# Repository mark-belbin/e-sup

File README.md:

# eSUP
HW and FW for motorized stand up paddle board (SUP). Includes BMS+Charger, MCU, and Battery-Holder PCBA designs.

## Motivation
1. Cruise around Foster City on a battery powered electric SUP.
2. Learn more about BMS HW and design.
3. Improve STM32 FW skills and knowledge.

## High-Level Block Diagram
Some aspects still TBD, but this is the general idea so far. BMS+Charger PCBA, Battery-Holder PCBAs, and MCU PCBA. May or may not need another custom PCBA for hand controller, might be possible to directly use or modify an OTS hand controller normally used for electric foil boards or skateboards.

## Battery Configuration

## Power Architecture

## Mechanical Design

## PCBA Design

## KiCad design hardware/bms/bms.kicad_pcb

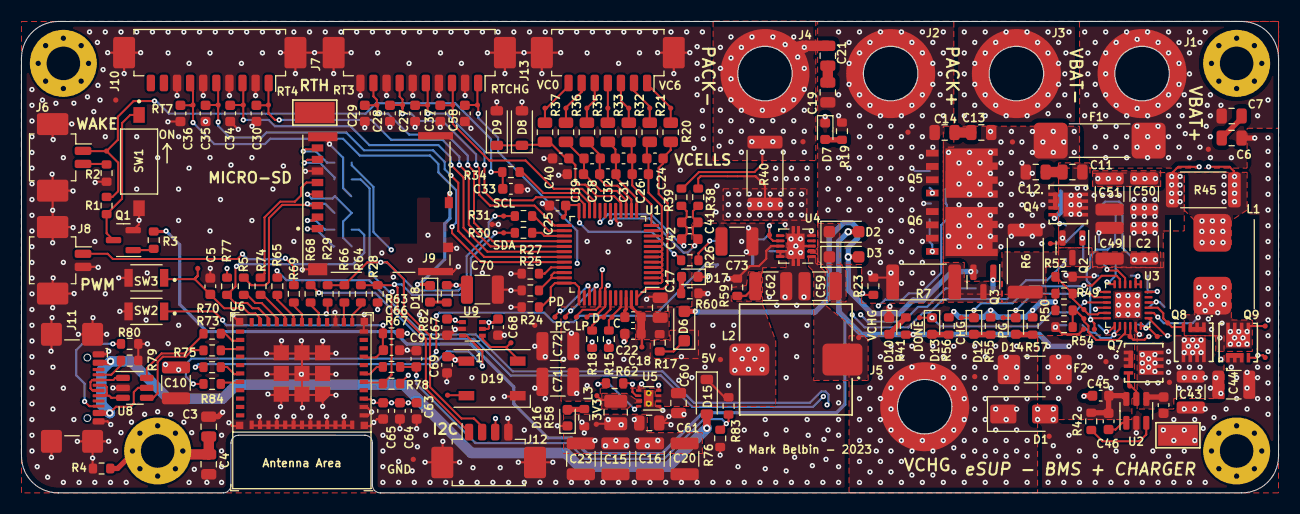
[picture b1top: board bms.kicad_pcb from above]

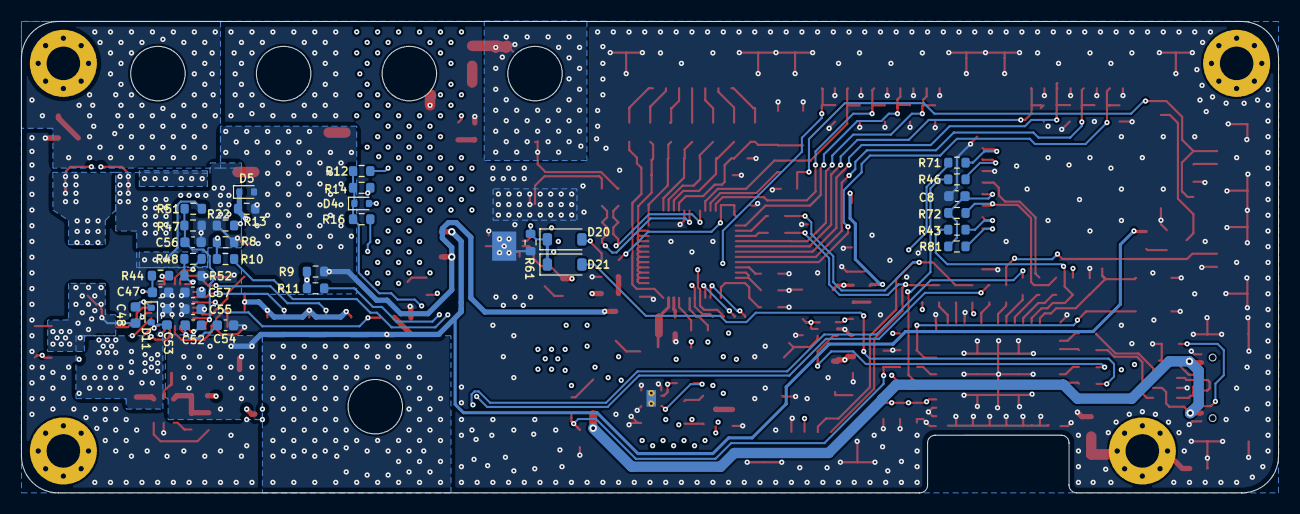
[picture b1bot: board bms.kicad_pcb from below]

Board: 4 copper layers, 120.0 x 45.0 mm, 287 parts (34 on the bottom side), 144 nets.

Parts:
C1, C5, C8, C9, C33, C42, C45, C46, C48, C52, C54, C65, C67, C68, C69: 0.1uF; C_0603_1608Metric
C2, C43, C44, C49, C50, C51: 10uF; C_1210_3225Metric
C3, C4, C6, C7, C11, C12, C13, C14, C19, C21: 0.1uF; C_0805_2012Metric
C10, C15, C16, C20, C23, C70, C71, C72, C73: 100uF; C_1210_3225Metric
C17: 1uF; C_0805_2012Metric
C18, C41: 100pF; C_0603_1608Metric
C22: 470nF; C_0603_1608Metric
C24, C26, C31, C32, C38, C39, C40: 220nF; C_0603_1608Metric
C25: 2.2uF; C_0603_1608Metric
C27, C28, C29, C30, C34, C35, C36, C37, C58: 1nF; C_0603_1608Metric
C47, C53, C55, C66: 1uF; C_0603_1608Metric
C56: 22pF; C_0603_1608Metric
C57: 56nF; C_0603_1608Metric
C59: 2.2uF; C_1210_3225Metric
C60: 10uF; C_0805_2012Metric
C61: 22uF; C_0805_2012Metric
C62: 47uF; C_1210_3225Metric
C63, C64: 10uF; C_0603_1608Metric
D1: SMAJ28A; D_SMA
D2, D3, D6: D_Schottky; D_SOD-123F
D4, D5: D_Zener; D_SOD-523
D7, D10, D13: BLUE; LED_0603_1608Metric
D8, D15, D20, D21: D_Schottky; D_SOD-123
D9: D_Zener; D_SOD-123
D11: D_Schottky; D_SOD-523
D12: AMBER; LED_0603_1608Metric
D14, D16, D17, D18: GREEN; LED_0603_1608Metric
D19: WS2812B; LED_WS2812B_PLCC4_5.0x5.0mm_P3.2mm
F1: 60A; SF-3812F6000T-2
F2: 15A; FUSC6125X279N
H1, H2, H3, H4: MountingHole_Pad; MountingHole_3.2mm_M3_Pad_Via
J1, J2, J3, J4, J5: Screw_Terminal_01x01; Wurth_746600430R
J6, J8: Conn_01x02; Molex_PicoBlade_53261-0271_1x02-1MP_P1.25mm_Horizontal
J7, J10: Conn_01x10; Molex_PicoBlade_53261-1071_1x10-1MP_P1.25mm_Horizontal
J9: Micro_SD_Card_Det2; MOLEX_503398-1892
J11: USB_C_Receptacle_USB2.0; USB_C_Receptacle_GCT_USB4110
J12: Conn_01x03; Molex_PicoBlade_53261-0471_1x04-1MP_P1.25mm_Horizontal
J13: Conn_01x07; Molex_PicoBlade_53261-0771_1x07-1MP_P1.25mm_Horizontal
L1: 3.3uH; IND_ETQP5M3R3YFK
L2: 150uH; IND_1050P-WE-PD_WRE-L
L3: 3.3uH; L_1008_2520Metric
NT1, NT2, NT4, NT5: Net-Tie; NetTie-2_SMD_Pad_8mil
Q1: MMBT3904; SOT-23
Q2, Q3: Q_PMOS_GSD; SOT-23
Q4, Q7, Q8, Q9: BSZ018N04LS6ATMA1; PG-TSDSON-8-26_INF
Q5, Q6: IAUC120N04S6N006ATMA1; PG-TDSON-8
R1, R2, R18, R19, R22, R23, R41, R42, R63, R71, R72, R76, R77, R78, R81, R83: 10k; R_0603_1608Metric
R3, R26, R55, R57, R58, R60, R82, R84: 1k; R_0603_1608Metric
R4, R8, R9, R12, R13: 10M; R_0603_1608Metric
R5, R24, R27, R30, R31, R34, R43, R46, R64, R65, R66, R67, R68, R69, R70, R73, R74, R75: 0R; R_0603_1608Metric
R6, R7: 1k; R_2512_6332Metric
R10, R11, R15, R79, R80: 5.1k; R_0603_1608Metric
R14, R16: 51; R_0603_1608Metric
R17, R38, R39, R56: 100R; R_0603_1608Metric
R20, R21, R32, R33, R35, R36, R37: 30R; R_0805_2012Metric
R25, R49, R50, R62: 100k; R_0603_1608Metric
R28, R29: 2.2k; R_0603_1608Metric
R40: 1m; R_2512_6332Metric
R44: 10R; R_0603_1608Metric
R45: 10m; R_2512_6332Metric
R47: 330k; R_0603_1608Metric
R48: 9.31k; R_0603_1608Metric
R51: 30k; R_0603_1608Metric
R52: 430k; R_0603_1608Metric
R53: 137k; R_0603_1608Metric
R54: 44.2k; R_0603_1608Metric
R59: 0.11R; R_0603_1608Metric
R61: 1.5M; R_0603_1608Metric
SW1: SW_SPST; SW_DS04-254-2-01BK-SMT-TR
SW2, SW3: SW_Push; SW_B3U-1000P
TP1, TP2, TP3, TP4, TP5, TP6, TP7, TP8, TP9, TP10, TP11, TP12, TP13, TP14, TP15, TP16, TP19, TP20, TP21, TP22, TP23, TP24, TP25, TP26, TP27, TP28, TP29, TP30, TP31, TP32, TP33, TP34, TP35, TP36, TP37, TP38, TP39, TP40, TP42, TP43, TP44, TP45, TP46, TP47, TP48, TP49, TP50, TP51, TP52, TP53, TP54, TP55, TP56, TP57, TP58, TP59, TP60, TP61, TP62, TP63, TP64: TestPoint; TestPoint_Pad_D0.5mm
TP17, TP18: TestPoint; TestPoint_Keystone_5019_Minature
U1: BQ76952; TQFP-48_7x7mm_P0.5mm
U2: LM74700; SOT-23-6
U3: BQ24610; VQFN-24-1EP_4x4mm_P0.5mm_EP2.45x2.45mm
U4: LM5166X; Texas_S-PVSON-N10_ThermalVias
U5: TPS62172DSG; WSON-8-1EP_2x2mm_P0.5mm_EP0.9x1.6mm_ThermalVias
U6: ESP32-C3-MINI-1-N4; ESP32-C3-MINI-1
U8: USBLC6-2SC6; SOT-23-6
U9: TXU0101DCKR; SOT-363_SC-70-6

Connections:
+3V3: C8.1, C10.1, C15.1, C16.1, C20.1, C23.1, C61.1, C63.1, C64.1, C65.1, C67.1, C70.1, J9.4 (VDD), J12.3, L3.2, R28.1, R29.1, R58.2, R62.2, R63.1, R71.1, R72.1, R77.1, R78.1, R81.1, R82.2, TP60.1, U5.6 (VOS), U6.3 (3V3), U9.1 (VCCA)
+5V: C60.1, C68.1, C69.1, C71.1, C72.1, C73.1, D15.1 (K), D19.1 (VDD), L2.2, R59.2, R60.2, R83.1, TP58.1, U4.8 (VOUT), U5.2 (VIN), U5.3 (EN), U9.5 (OE), U9.6 (VCCB)
/BATTERY BALANCE AND MONITOR/CGATE: D5.1 (K), Q4.2 (G), R13.2, R15.1
/BATTERY BALANCE AND MONITOR/CHG: R15.2, TP7.1, U1.45 (CHG)
/BATTERY BALANCE AND MONITOR/DGATE: D4.1 (K), R12.2, R14.2, R16.2, R18.1
/BATTERY BALANCE AND MONITOR/DSG: R18.2, TP8.1, U1.43 (DSG)
/BATTERY BALANCE AND MONITOR/I2C_SCL: J12.2, R29.2, R31.2, R66.1, TP22.1
/BATTERY BALANCE AND MONITOR/I2C_SDA: J12.1, R28.2, R30.2, R64.1, TP21.1
/BATTERY BALANCE AND MONITOR/LD: R23.1, TP15.1, U1.41 (LD)
/BATTERY BALANCE AND MONITOR/PACK: R22.1, TP14.1, U1.42 (PACK)
/BATTERY BALANCE AND MONITOR/PACK+: C14.2, C19.2, D4.2 (A), J2.1, Q5.1 (S), Q6.1 (S), R7.2, R12.1, R19.1, R23.2, TP4.1
/BATTERY BALANCE AND MONITOR/PACK-: C21.1, J4.1, NT2.2, R40.1, TP9.1
/BATTERY BALANCE AND MONITOR/PCGATE: Q2.1 (G), R8.2, R10.1
/BATTERY BALANCE AND MONITOR/PCHG: R10.2, TP10.1, U1.40 (PCHG)
/BATTERY BALANCE AND MONITOR/PDGATE: Q3.1 (G), R9.2, R11.1
/BATTERY BALANCE AND MONITOR/PDSG: R11.2, TP12.1, U1.39 (PDSG)
/BATTERY BALANCE AND MONITOR/PWR_EN: D20.2 (A), R26.1
/BATTERY BALANCE AND MONITOR/REG18: C25.1, R26.2, TP16.1, U1.24 (REG18)
/BATTERY BALANCE AND MONITOR/RST_SHUT: R27.1, U1.33 (RST_SHUT)
/BATTERY BALANCE AND MONITOR/SCL_BMGT: R31.1, U1.26 (SCL)
/BATTERY BALANCE AND MONITOR/SDA_BMGT: R30.1, U1.27 (SDA)
/BATTERY BALANCE AND MONITOR/SRN: C41.1, C42.1, R39.1, U1.20 (SRN)
/BATTERY BALANCE AND MONITOR/SRP: C41.2, C42.2, R38.1, U1.18 (SRP)
/BATTERY BALANCE AND MONITOR/TS2: R34.1, U1.22 (WAKE/TS2)
/BATTERY BALANCE AND MONITOR/VC0: C40.1, D8.1 (K), D9.1 (K), R37.1, U1.16 (VC0)
/BATTERY BALANCE AND MONITOR/VC1: C38.2, C39.1, R36.1, U1.15 (VC1)
/BATTERY BALANCE AND MONITOR/VC2: C32.2, C38.1, R35.1, U1.14 (VC2)
/BATTERY BALANCE AND MONITOR/VC3: C31.2, C32.1, R33.1, U1.13 (VC3)
/BATTERY BALANCE AND MONITOR/VC4: C26.2, C31.1, R32.1, U1.12 (VC4)
/BATTERY BALANCE AND MONITOR/VC15: C24.2, C26.1, R21.1, U1.1 (VC15), U1.2 (VC14), U1.3 (VC13), U1.4 (VC12), U1.5 (VC11), U1.6 (VC10), U1.7 (VC9), U1.8 (VC8), U1.9 (VC7), U1.10 (VC6), U1.11 (VC5)
/BATTERY BALANCE AND MONITOR/VC16: C24.1, R20.1, U1.48 (VC16)
/BATTERY BALANCE AND MONITOR/VCHG+: C2.1, C11.1, C49.1, C50.1, C51.1, C56.1, NT5.1, Q2.2 (S), Q4.3 (D), R8.1, R22.2, R45.1, R47.2, TP3.1
/BATTERY CHARGER/BTST: C48.2, D11.1 (K), U3.22 (BTST)
/BATTERY CHARGER/CHG_IN_PROT: C1.2, C43.1, C44.1, Q7.3 (D), Q8.3 (D), R44.1, TP38.1, U2.4 (CATHODE), U3.1 (ACN), U3.2 (ACP)
/BATTERY CHARGER/C_VCC: C47.1, R44.2, U3.24 (VCC)
/BATTERY CHARGER/DG: Q7.2 (G), TP39.1, U2.5 (GATE)
/BATTERY CHARGER/DRV_HI: Q8.2 (G), TP40.1, U3.21 (HIDRV)
/BATTERY CHARGER/DRV_LO: Q9.2 (G), TP44.1, U3.19 (LODRV)
/BATTERY CHARGER/ISET1: R49.1, R53.2, TP48.1, U3.11 (ISET1)
/BATTERY CHARGER/ISET2: R50.1, R54.2, TP49.1, U3.15 (ISET2)
/BATTERY CHARGER/REGEN: C53.1, D11.2 (A), TP43.1, U3.18 (REGEN)
/BATTERY CHARGER/SRN_CHG: C52.1, NT5.2, U3.13 (SRN)
/BATTERY CHARGER/SRP_CHG: C52.2, C54.1, NT4.2, U3.14 (SRP)
/BATTERY CHARGER/SW_NODE: C48.1, L1.1, Q8.1 (S), Q9.3 (D), TP42.1, U3.20 (PH)
/BATTERY CHARGER/TTC: C57.1, U3.7 (TTC)
/BATTERY CHARGER/VFB: C56.2, R47.1, R51.2, TP46.1, U3.12 (VFB)
/BATTERY CHARGER/VREF: C55.1, R48.2, R49.2, R50.2, R55.2, R56.2, R57.2, TP45.1, U3.4 (CE), U3.10 (VREF), U3.16 (ACSET)
/BATTERY CHARGER/~PG: D14.1 (K), TP56.1, U3.8 (~PG)
/BMS_WAKE: C33.2, J6.1, R1.1, R34.2, TP29.1
/CHG_STAT1: D12.1 (K), R65.1, TP54.1, U3.5 (STAT1)
/CHG_STAT2: D13.1 (K), R68.2, TP55.1, U3.9 (STAT2)
/MCU/3V3_SW: L3.1, TP59.1, U5.7 (SW)
/MCU/5V_DETECT: C9.1, R67.1, R76.1, R83.2
/MCU/5V_EN: D20.1 (K), D21.1 (K), R61.2, TP61.1, U4.7 (EN)
/MCU/5V_SW: L2.1, TP57.1, U4.1 (SW)
/MCU/BOOT: C5.1, SW3.1, TP62.1, U6.23 (IO9)
/MCU/CS: J9.2 (DAT3/CD), R43.2
/MCU/EN: C66.1, R63.2, SW2.1, U6.8 (EN)
/MCU/GPIO0: R64.2, U6.12 (IO0)
/MCU/GPIO1: R66.2, U6.13 (IO1)
/MCU/GPIO2: R46.2, R78.2, U6.5 (IO2)
/MCU/GPIO3: R67.2, U6.6 (IO3)
/MCU/GPIO4: R69.2, U6.18 (IO4)
/MCU/GPIO5: R65.2, U6.19 (IO5)
/MCU/GPIO6: R74.2, U6.20 (IO6)
/MCU/GPIO7: R5.1, U6.21 (IO7)
/MCU/GPIO8: R43.1, R77.2, U6.22 (IO8)
/MCU/GPIO10: R68.1, U6.16 (IO10)
/MCU/GPIO18: R70.1, U6.26 (IO18/USB_D-)
/MCU/GPIO19: R73.1, U6.27 (IO19/USB_D+)
/MCU/GPIO20: R75.2, U6.30 (RXD0)
/MCU/GPIO21: R84.1, U6.31 (TXD0)
/MCU/MCU_VIN: C59.1, D2.1 (K), D3.1 (K), U4.2 (VIN)
/MCU/MISO: J9.7 (DAT0), R46.1
/MCU/MOSI: J9.3 (CMD), R5.2, R72.2
/MCU/PG: R62.1, U5.8 (PG)
/MCU/PWM_OUT: J8.1, R69.1
/MCU/RGB_DIN: D19.4 (DIN), TP63.1, U9.4 (Y)
/MCU/RGB_DIN_ESP: R75.1, U9.3 (A)
/MCU/RGB_DOUT: D19.2 (DOUT), TP64.1
/MCU/SCLK: J9.5 (CLK), R74.1
/MCU/SD_CARD_WRITE: D21.2 (A), R84.2
/THERM_0: C37.1, J7.3, TP33.1, U1.21 (TS1)
/THERM_1: C27.1, J7.5, TP23.1, U1.23 (TS3)
/THERM_2: C28.1, J7.7, TP24.1, U1.25 (ALERT/TS4)
/THERM_3: C29.1, J7.9, TP25.1, U1.28 (HDQ/TS5)
/THERM_4: C30.1, J10.1, TP26.1, U1.29 (CFETOFF/TS6)
/THERM_5: C34.1, J10.3, TP30.1, U1.30 (DFETOFF/TS7)
/THERM_6: C35.1, J10.5, TP31.1, U1.31 (DCHG/TS8)
/THERM_7: C36.1, J10.7, TP32.1, U1.32 (DDSG/TS9)
/THERM_CHG: C58.1, J7.1, R48.1, R52.2, TP47.1, U3.6 (TS)
/USB_D+: R73.2, U8.4 (I/O2)
/USB_D+_CONN: J11.A6 (D+), J11.B6 (D+), U8.3 (I/O2)
/USB_D-: R70.2, U8.6 (I/O1)
/USB_D-_CONN: J11.A7 (D-), J11.B7 (D-), U8.1 (I/O1)
/VBAT_IN: C7.2, F1.1, J1.1, TP1.1
/VBAT_IN_F: C12.2, C13.1, D3.2 (A), D5.2 (A), D6.2 (A), F1.2, Q3.2 (S), Q4.1 (S), Q5.3 (D), Q6.3 (D), R6.2, R9.1, R13.1, TP5.1
/VCHG_IN: D1.1 (A1), F2.1, J5.1, TP2.1
/VCHG_IN_F: C45.2, C46.2, D2.2 (A), F2.2, Q7.1 (S), R3.2, R41.1, R42.1, TP37.1, U2.6 (ANODE)
/VUSB_5V: D15.2 (A), J11.A4 (VBUS), J11.A9 (VBUS), J11.B4 (VBUS), J11.B9 (VBUS), U8.5 (VBUS)
/V_CELLS_0: J13.7, R37.2, TP36.1
/V_CELLS_1: J13.6, R36.2, TP35.1
/V_CELLS_2: J13.5, R35.2, TP34.1
/V_CELLS_3: J13.4, R33.2, TP28.1
/V_CELLS_4: J13.3, R32.2, TP27.1
/V_CELLS_5: J13.2, R21.2, TP13.1
/V_CELLS_6: J13.1, R20.2, TP11.1
GND: C1.1, C2.2, C3.2, C4.2, C5.2, C6.1, C8.2, C9.2, C10.2, C15.2, C16.2, C17.2, C18.2, C20.2, C23.2, C25.2, C27.2, C28.2, C29.2, C30.2, C33.1, C34.2, C35.2, C36.2, C37.2, C39.2, C40.2, C43.2, C44.2, C45.1, C47.2, C49.2, C50.2, C51.2, C53.2, C54.2, C55.2, C57.2, C58.2, C59.2, C60.2, C61.2, C62.2, C63.2, C64.2, C65.2, C66.2, C67.2, C68.2, C69.2, C70.2, C71.2, C72.2, C73.2, D1.2 (A2), D7.1 (K), D8.2 (A), D9.2 (A), D10.1 (K), D16.1 (K), D17.1 (K), D19.3 (VSS), J3.1, J6.MP (MountPin), J7.2, J7.4, J7.6, J7.8, J7.10, J7.MP (MountPin), J8.2, J8.MP (MountPin), J9.6 (VSS), J9.9 (DET_B), J9.11 (SHIELD), J10.2, J10.4, J10.6, J10.8, J10.MP (MountPin), J11.A1 (GND), J11.A12 (GND), J11.B1 (GND), J11.B12 (GND), J11.S1 (SHIELD), J12.4, J12.MP (MountPin), J13.MP (MountPin), NT1.2, Q1.2 (E), Q9.1 (S), R2.2, R4.1, R24.2, R25.2, R27.2, R40.2, R51.1, R52.1, R53.1, R54.1, R61.1, R76.2, R79.1, R80.1, SW1.2 (B), SW2.2, SW3.2, TP17.1, TP18.1, TP19.1, TP20.1, TP50.1, TP51.1, TP52.1, TP53.1, U1.17 (VSS), U2.2 (GND), U3.17 (GND), U3.25 (GND), U4.3 (ILIM), U4.5 (RT), U4.9 (HYS), U4.10 (GND), U4.11 (PAD), U5.1 (PGND), U5.4 (AGND), U5.5 (FB), U5.9 (PAD), U6.1 (GND), U6.2 (GND), U6.11 (GND), U6.14 (GND), U6.36 (GND), U6.37 (GND), U6.38 (GND), U6.39 (GND), U6.40 (GND), U6.41 (GND), U6.42 (GND), U6.43 (GND), U6.44 (GND), U6.45 (GND), U6.46 (GND), U6.47 (GND), U6.48 (GND), U6.49 (GND_EP), U6.50 (GND), U6.51 (GND), U6.52 (GND), U6.53 (GND), U8.2 (GND), U9.2 (GND)
GNDPWR: C3.1, C4.1, H1.1, R4.2
unnamed: C6.2, C7.1
unnamed: C11.2, C12.1
unnamed: C13.2, C14.1
unnamed: C19.1, C21.2
unnamed: C62.1, R59.1
unnamed: D6.1 (K), R17.1
unnamed: D7.2 (A), R19.2
unnamed: D10.2 (A), R41.2
unnamed: D12.2 (A), R55.1
unnamed: D13.2 (A), R56.1
unnamed: D14.2 (A), R57.1
unnamed: D16.2 (A), R58.1
unnamed: D17.2 (A), R60.1
unnamed: D18.2 (A), R82.1
unnamed: D18.1 (K), J9.10 (DET_A)
unnamed: J6.2, R2.1
unnamed: J9.8 (DAT1), R71.2
unnamed: J9.1 (DAT2), R81.2
unnamed: J11.A5 (CC1), R79.2
unnamed: J11.B5 (CC2), R80.2
unnamed: L1.2, NT4.1, R45.2
unnamed: NT1.1, R38.2
unnamed: NT2.1, R39.2
unnamed: Q1.1 (B), R3.1
unnamed: Q1.3 (C), R1.2, SW1.1 (A)
unnamed: Q2.3 (D), R6.1
unnamed: Q3.3 (D), R7.1
unnamed: Q5.2 (G), R14.1
unnamed: Q6.2 (G), R16.1
unnamed: C17.1, C18.1, C22.2, R17.2, TP6.1, U1.47 (BAT)
unnamed: R24.1, U1.36 (REGIN), U1.37 (BREG)
unnamed: C22.1, U1.46 (CP1)
unnamed: R25.1, U1.34 (REG2), U1.35 (REG1)
unnamed: R42.2, U2.3 (EN)
unnamed: C46.1, U2.1 (VCAP)

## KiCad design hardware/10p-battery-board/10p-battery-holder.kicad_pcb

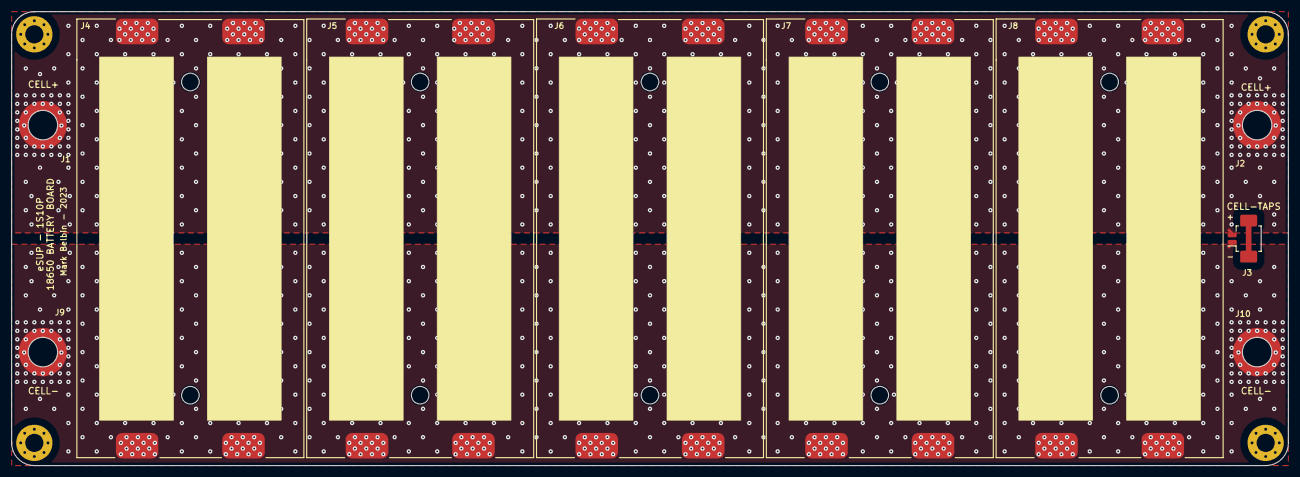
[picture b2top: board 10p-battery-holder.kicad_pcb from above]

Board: 2 copper layers, 225.0 x 80.0 mm, 14 parts (0 on the bottom side), 2 nets.

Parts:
H1, H2, H3, H4: MountingHole_Pad; MountingHole_3.2mm_M3_Pad_Via
J1, J2, J9, J10: Screw_Terminal_01x01; Wurth_746600430R
J3: Conn_01x02; Molex_PicoBlade_53261-0271_1x02-1MP_P1.25mm_Horizontal
J4, J5, J6, J7, J8: dual_18650_battery_holder

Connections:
/CELL+: J1.1, J2.1, J3.2, J4.1 (CELL1+), J4.2 (CELL2+), J5.1 (CELL1+), J5.2 (CELL2+), J6.1 (CELL1+), J6.2 (CELL2+), J7.1 (CELL1+), J7.2 (CELL2+), J8.1 (CELL1+), J8.2 (CELL2+)
/CELL-: J3.1, J4.3 (CELL1-), J4.4 (CELL2-), J5.3 (CELL1-), J5.4 (CELL2-), J6.3 (CELL1-), J6.4 (CELL2-), J7.3 (CELL1-), J7.4 (CELL2-), J8.3 (CELL1-), J8.4 (CELL2-), J9.1, J10.1

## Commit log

2023-10-09 Initial README update
    Added high level block diagram and some initial details.
2023-10-09 added existing CAD SolidWorks files plus docs
2023-10-09 More quick README thoughts
2023-10-09 created bms PCBA project
2023-10-09 added template sch pages
2023-10-10 Created battery manager and charger IC symbols.
2023-10-11 More progress on battery management circuit
2023-10-16 Battery monitor / balancer schematic complete. Charger is next. Thinking of adding MCU directly to this board if layout space allows, probably doesn't deserve its own board (or just deserves a dev bo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
2023-10-16 Selected connectors for cell taps, in/out power, charger, and enable switch.
2023-10-18 Created footprints for microfit and wurth screw terminals
2023-10-21 Resaved projected with KiCAD v7
2023-10-22 Added charger and pack fuses directly to board
2023-10-23 More charger sch progress
2023-10-23 Added another thermistor for charger temp sensings. 9 total for the whole pack now
2023-10-24 Made more progress on charger sch. Need to complete power stage next. Also added diode OR for MCU power conv input. Still deciding on converter selection
2023-10-25 Selected charger FETs, replaced other charger FETs to match. FETs rated for 40V since this is a 6S board (25.2V MAX). Also downsized the discharge FETs to be smaller and cheaper by selecting 40V FETs.
2023-10-26 Charger schematic complete! Only MCU left.
2023-10-27 Choose MCU as ESP32-C3-MINI. Small form factor with just enough I/O.
2023-10-28 Added BJT to enable BMS/MCU when charger input voltage present
2023-10-29 Selected power conversion scheme and converters.
2023-10-29 MCU power conversion section complete
2023-10-29 Sch mostly complete! Just have the USB C connector left to sort out.
2023-10-29 Updated USB C connector, fixed all sch ERC errors, imported footprints into pcb file, fixed any pcb import errors.
2023-10-29 Sch cleanup, added extra netties
2023-10-31 Continued layout, defined board area based on mech assembly
2023-11-01 Updated test points to 0.5mm to save space, continued layout
2023-11-01 Simplified chassis connection, only at one mounting hole and left other holes NC (no chassis plane on PCB
2023-11-01 Some routing for thermistors and cell taps to see if it works
2023-11-01 refined routing near cell taps
2023-11-03 More layout, changed precharge / predischarged PMOS selection to SOT-23 size to save space. Charger layout will be difficult, may need to change charger input terminal location...
2023-11-04 Changed large input fuse, slightly smaller and cheaper, 60A rated. Layout more defined, charger layout much better now
2023-11-05 Added Micro SD card circuit.
2023-11-05 Layout complete! MicroSD card fits just fine
2023-11-05 Modified layout to fit inside enclosure and around penetrators. Routing time!
2023-11-06 Power plane and thermal vias for charger and FETs section
2023-11-06 Few cross-board connections made, a bit tricky to work around power planes
2023-11-07 Added extra features to try and prevent SD card data corruption. Added override enable so that the MCU can keep itself on until the SD card is finished writing, also added 5V / wake detect circuit so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
2023-11-07 Added bulk cap for 5V and 3V3 rails, made sure they fit in current layout
2023-11-08 Swapped out SD card holder to a push-push version, should be nicer. Also a lot of routing and power plane work
2023-11-08 More routing, just 3V3 and 5V power planes to go, then ground via stiching
2023-11-09 Working through DRC errors. All nets connected, need to double check JLCPCB design rules
2023-11-10 Added board cutout for antenna, recommended by ESP32 docs
2023-11-10 All DRC errors cleared, updated design rules based off JLCs specs
2023-11-10 Board essentially finished! All silkscreen cleaned up, all DRC errors cleared.
2023-11-10 Added board dimensions to dimension layer
2023-11-11 Added keystone clip test points for ground, should be nice
2023-11-11 Updated silkscreen
2023-11-12 Review of BMS board looks good, finished!
2023-11-12 Created battery holder PCBA project, sch finished, basic board layout finished
2023-11-12 Finished battery holder board!
2023-11-13 Updated mech assembly with battery board, looks good. Ordering V1 PCBs!
2023-11-13 Exported gerbers for both boards
2023-11-16 Updated MFG PNs, BOM ordered.
2024-04-14 Updates for mechanical and pcba
2024-04-14 Added placeholder firmware folder
